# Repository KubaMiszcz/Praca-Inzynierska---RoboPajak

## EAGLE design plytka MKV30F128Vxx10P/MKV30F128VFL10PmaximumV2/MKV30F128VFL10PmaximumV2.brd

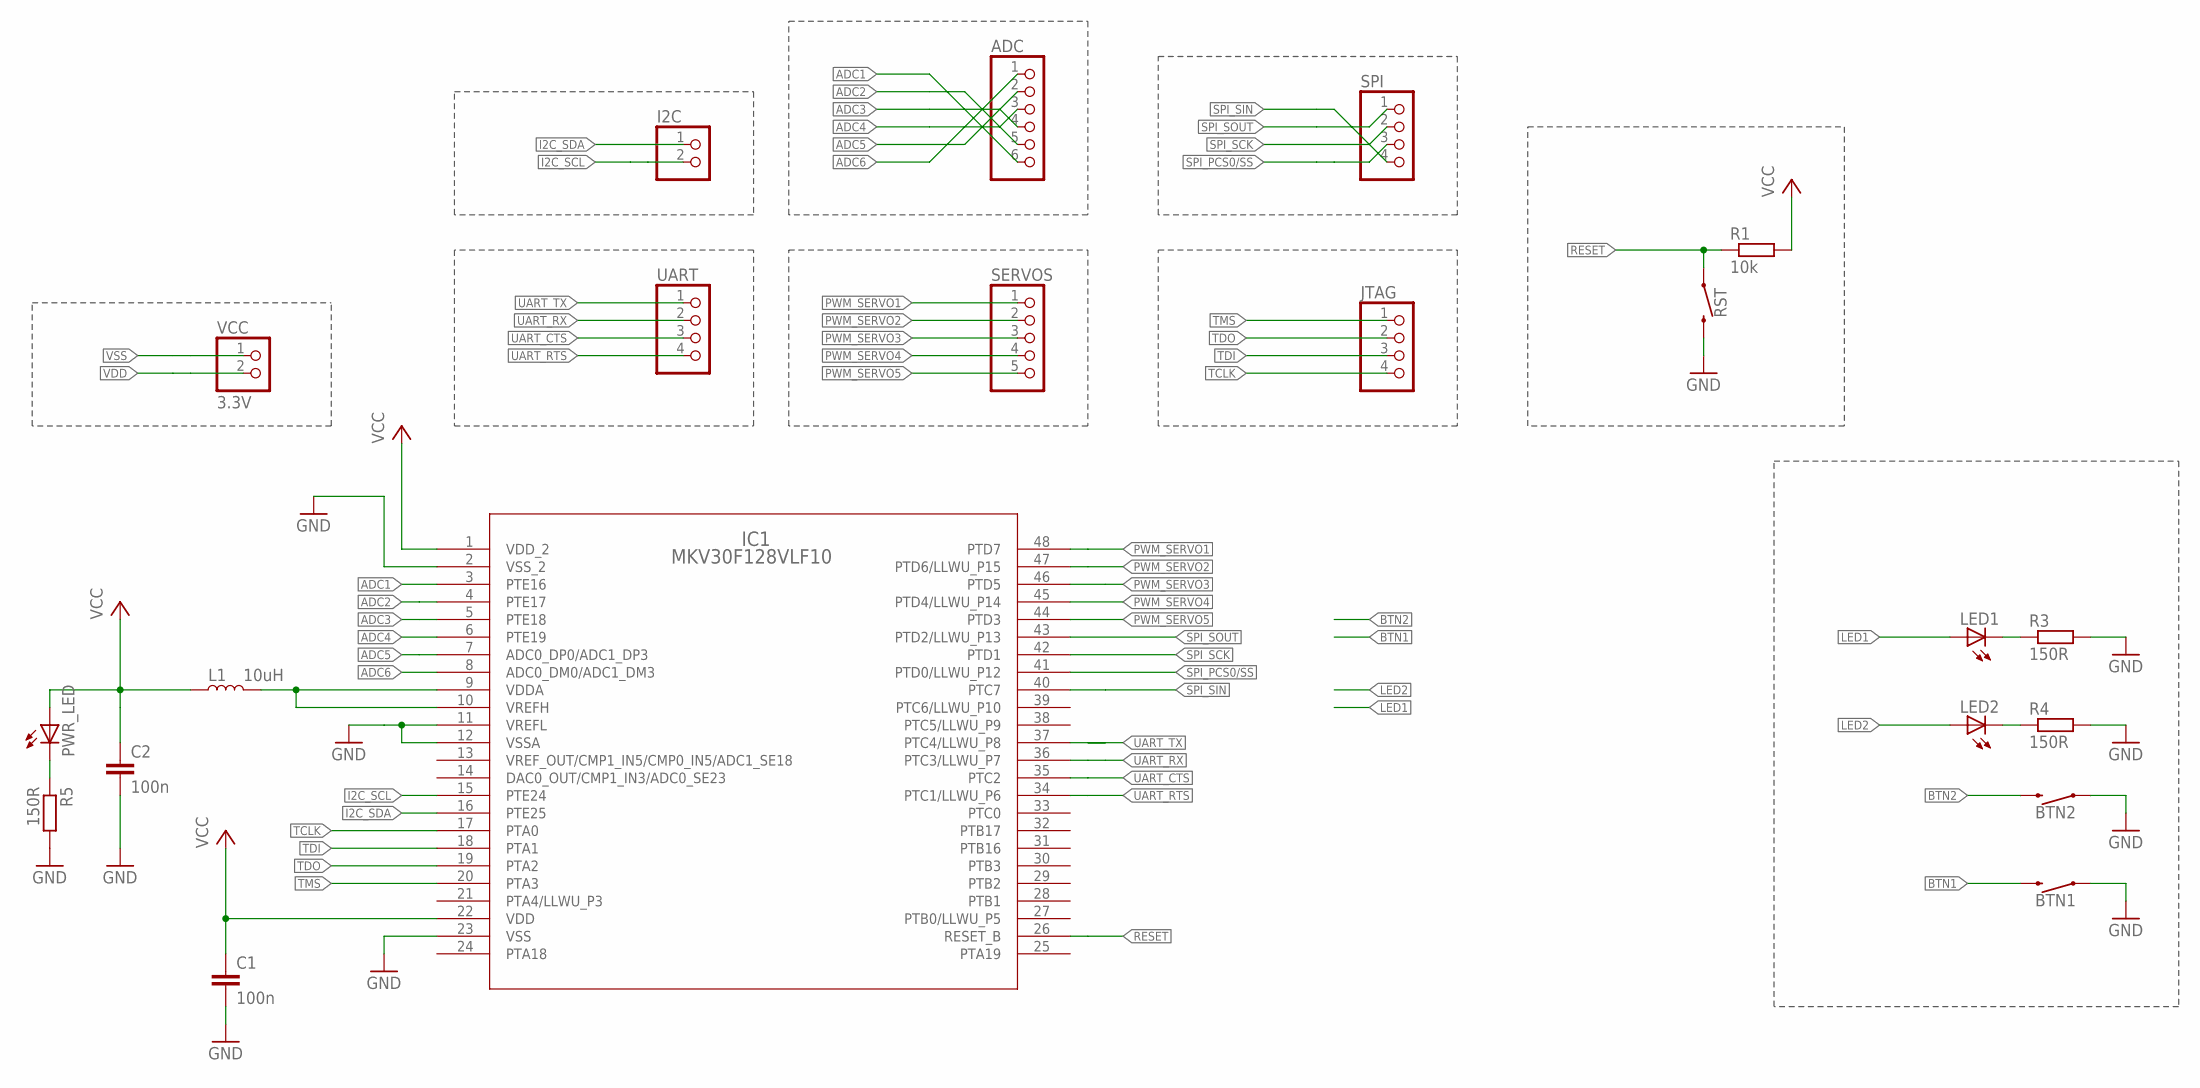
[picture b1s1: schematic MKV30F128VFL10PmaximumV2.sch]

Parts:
ADC: PINHD-1X6/90; 1X06/90
BTN1, BTN2: MOMENTARY-SWITCH-SPST-SMD-6.0X3.5MM; TACTILE_SWITCH_SMD_6.0X3.5MM
C1, C2: 100n; C0805
I2C: PINHD-1X2/90; 1X02/90
IC1: MKV30F128VLF10; LQFP-48_7X7X1.6
JTAG: PINHD-1X4/90; 1X04/90
L1: 10uH; 0805
LED1, LED2: LEDCHIP-LED0805; CHIP-LED0805
PWR_LED: LEDCHIP-LED0805; CHIP-LED0805
R1: 10k; R0805W
R3, R4, R5: 150R; R0805W
RST: MOMENTARY-SWITCH-SPST-SMD-6.0X3.5MM; TACTILE_SWITCH_SMD_6.0X3.5MM
SERVOS: PINHD-1X5/90; 1X05/90
SPI: PINHD-1X4/90; 1X04/90
UART: PINHD-1X4/90; 1X04/90
VCC: 3.3V; 1X02/90

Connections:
ADC1: ADC.6, IC1.3 (PTE16)
ADC2: ADC.5, IC1.4 (PTE17)
ADC3: ADC.4, IC1.5 (PTE18)
ADC4: ADC.3, IC1.6 (PTE19)
ADC5: ADC.2, IC1.7 (ADC0_DP0/ADC1_DP3)
ADC6: ADC.1, IC1.8 (ADC0_DM0/ADC1_DM3)
BTN1: BTN1.2
BTN2: BTN2.2
I2C_SCL: I2C.2, IC1.15 (PTE24)
I2C_SDA: I2C.1, IC1.16 (PTE25)
LED1: LED1.A
LED2: LED2.A
unnamed: LED2.C, R4.1
unnamed: LED1.C, R3.1
unnamed: PWR_LED.C, R5.1
PWM_SERVO1: IC1.48 (PTD7), SERVOS.1
PWM_SERVO2: IC1.47 (PTD6/LLWU_P15), SERVOS.2
PWM_SERVO3: IC1.46 (PTD5), SERVOS.3
PWM_SERVO4: IC1.45 (PTD4/LLWU_P14), SERVOS.4
PWM_SERVO5: IC1.44 (PTD3), SERVOS.5
RESET: IC1.26 (RESET_B), R1.1, RST.1
SPI_PCS0/SS: IC1.41 (PTD0/LLWU_P12), SPI.3
SPI_SCK: IC1.42 (PTD1), SPI.2
SPI_SIN: IC1.40 (PTC7), SPI.4
SPI_SOUT: IC1.43 (PTD2/LLWU_P13), SPI.1
TCLK: IC1.17 (PTA0), JTAG.4
TDI: IC1.18 (PTA1), JTAG.3
TDO: IC1.19 (PTA2), JTAG.2
TMS: IC1.20 (PTA3), JTAG.1
UART_CTS: IC1.35 (PTC2), UART.3
UART_RTS: IC1.34 (PTC1/LLWU_P6), UART.4
UART_RX: IC1.36 (PTC3/LLWU_P7), UART.2
UART_TX: IC1.37 (PTC4/LLWU_P8), UART.1
VDD: C1.1, C2.1, IC1.1 (VDD_2), IC1.22 (VDD), L1.1, PWR_LED.A, R1.2, VCC.2
VDDA: IC1.9 (VDDA), IC1.10 (VREFH), L1.2
VSS: BTN1.1, BTN2.1, C1.2, C2.2, IC1.2 (VSS_2), IC1.11 (VREFL), IC1.12 (VSSA), IC1.23 (VSS), R3.2, R4.2, R5.2, RST.2, VCC.1

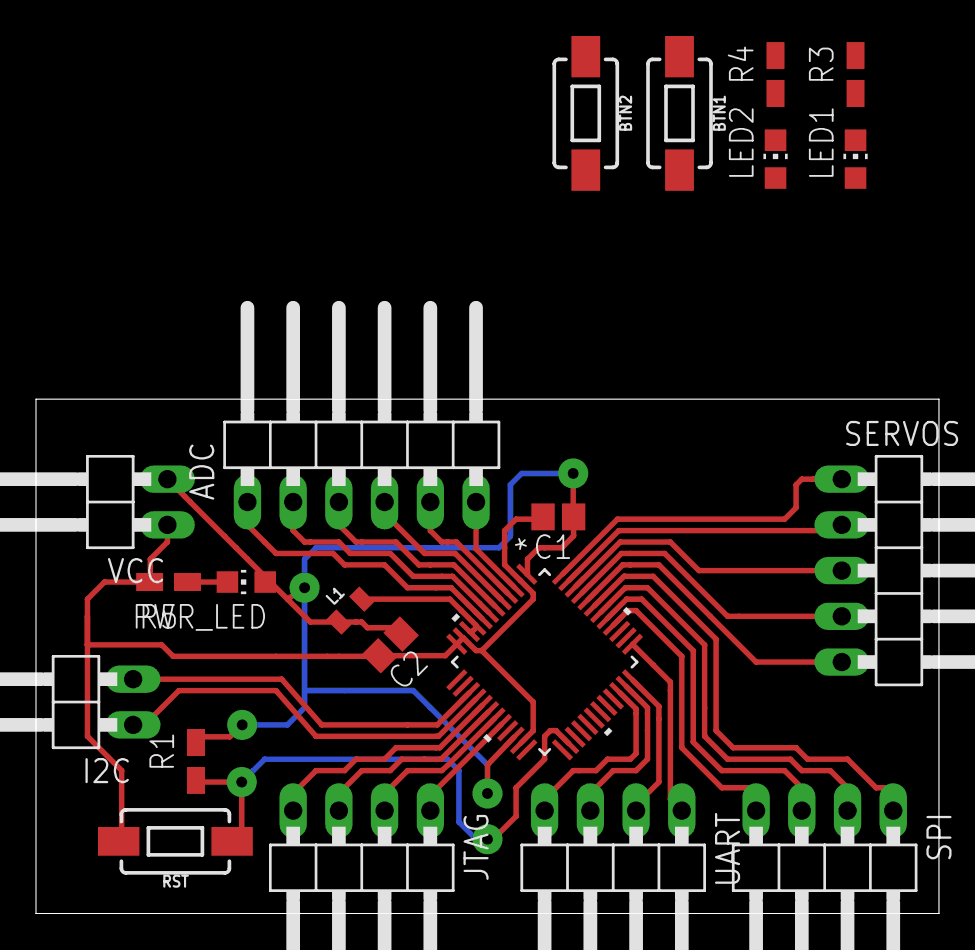
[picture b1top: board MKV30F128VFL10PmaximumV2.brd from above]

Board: 2 copper layers, 50.2 x 28.6 mm, 21 parts (0 on the bottom side), 32 nets.

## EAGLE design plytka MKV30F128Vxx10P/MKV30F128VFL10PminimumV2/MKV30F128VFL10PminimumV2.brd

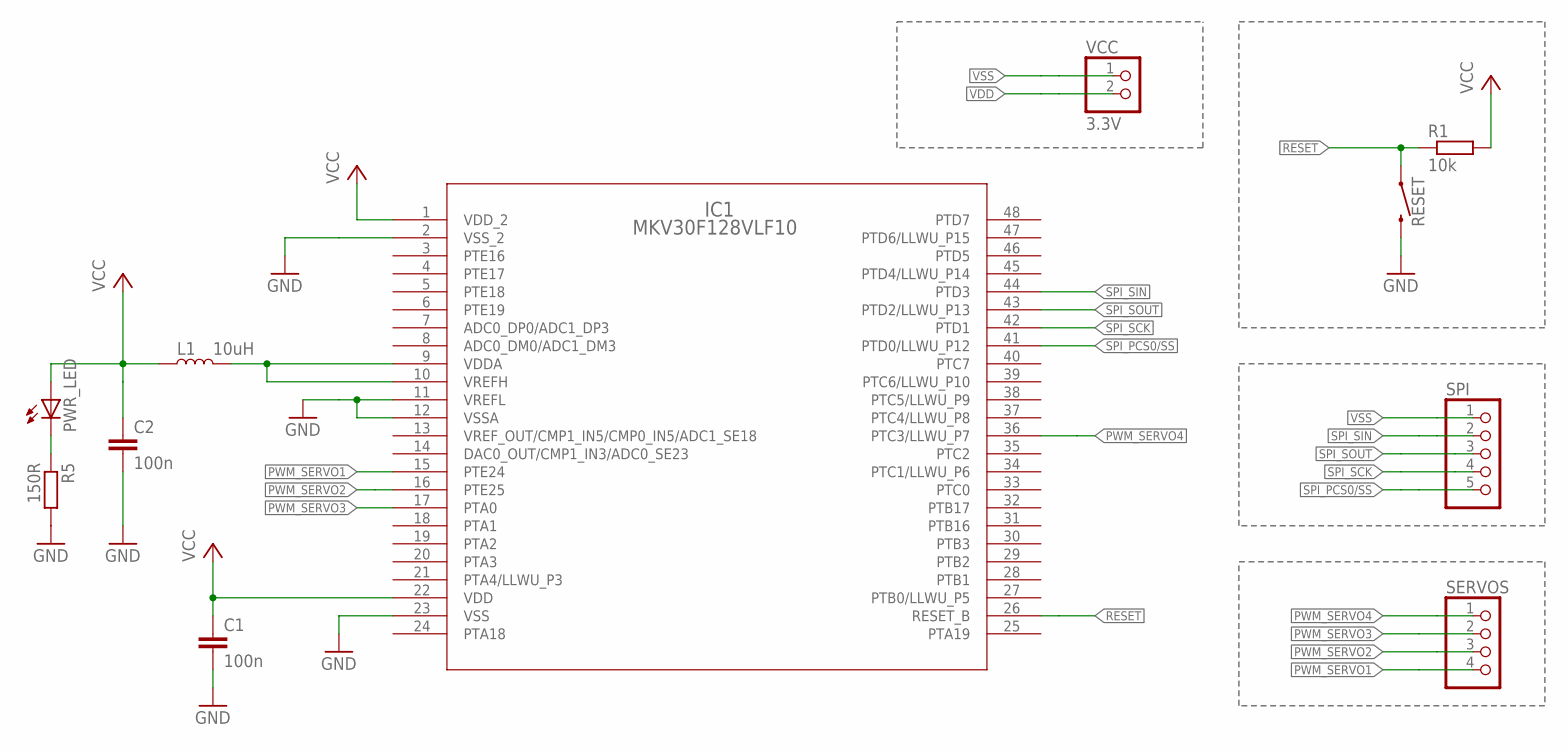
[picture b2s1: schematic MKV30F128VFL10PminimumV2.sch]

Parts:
C1, C2: 100n; C0805
IC1: MKV30F128VLF10; LQFP-48_7X7X1.6
L1: 10uH; 0805
PWR_LED: LEDCHIP-LED0805; CHIP-LED0805
R1: 10k; R0805W
R5: 150R; R0805W
RESET: MOMENTARY-SWITCH-SPST-SMD-6.0X3.5MM; TACTILE_SWITCH_SMD_6.0X3.5MM
SERVOS: PINHD-1X4/90; 1X04/90
SPI: PINHD-1X5/90; 1X05/90
VCC: 3.3V; 1X02/90

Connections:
unnamed: PWR_LED.C, R5.1
PWM_SERVO1: IC1.15 (PTE24), SERVOS.4
PWM_SERVO2: IC1.16 (PTE25), SERVOS.3
PWM_SERVO3: IC1.17 (PTA0), SERVOS.2
PWM_SERVO4: IC1.36 (PTC3/LLWU_P7), SERVOS.1
RESET: IC1.26 (RESET_B), R1.1, RESET.1
SPI_PCS0/SS: IC1.41 (PTD0/LLWU_P12), SPI.5
SPI_SCK: IC1.42 (PTD1), SPI.4
SPI_SIN: IC1.44 (PTD3), SPI.2
SPI_SOUT: IC1.43 (PTD2/LLWU_P13), SPI.3
VDD: C1.1, C2.1, IC1.1 (VDD_2), IC1.22 (VDD), L1.1, PWR_LED.A, R1.2, VCC.2
VDDA: IC1.9 (VDDA), IC1.10 (VREFH), L1.2
VSS: C1.2, C2.2, IC1.2 (VSS_2), IC1.11 (VREFL), IC1.12 (VSSA), IC1.23 (VSS), R5.2, RESET.2, SPI.1, VCC.1

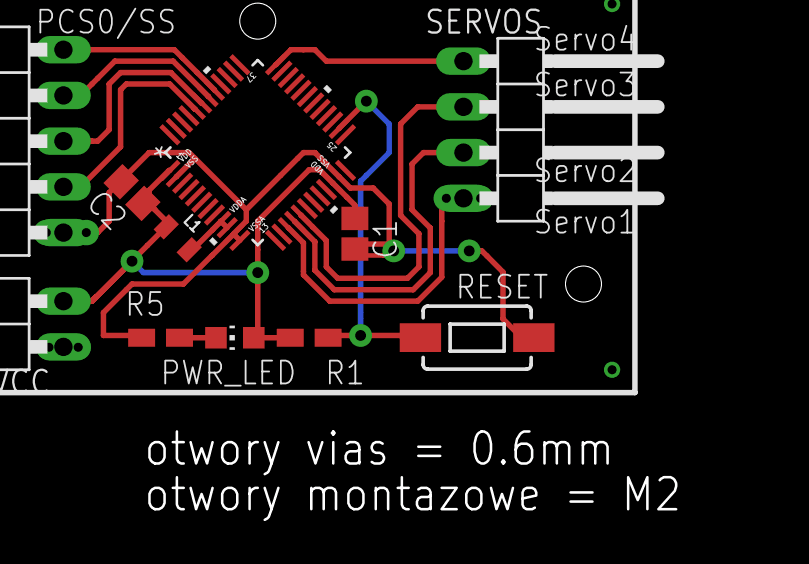
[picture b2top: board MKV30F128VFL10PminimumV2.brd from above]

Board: 2 copper layers, 11 parts (0 on the bottom side), 13 nets.

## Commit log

2017-03-20 :neckbeard: Added .gitattributes
2017-06-12 a
    a

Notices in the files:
parts and their libraries:
SparkFun-Switches: Licensing: Creative Commons ShareAlike 4.0 International - https://creativecommons.org/licenses/by-sa/4.0
